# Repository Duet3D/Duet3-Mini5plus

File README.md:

# Duet3-Mini5+
The Duet 3 Mini 5+ balances value and performance, focused on small and medium size machines that do not need the high power output of the Duet 3 Mainboard 6HC. 

Product page is here: https://www.duet3d.com/Duet3Mini5plus

Documentation is here: https://docs.duet3d.com/Duet3D_hardware/Duet_3_family/Duet_3_Mini_5+_Hardware_Overview

This repository also contains information in the Mini 2+ : a two driver expansion board for the Duet 3 mini 5+

Product page is here: https://www.duet3d.com/Duet3ExpansionMini2plus

Documentation is here: https://docs.duet3d.com/Duet3D_hardware/Duet_3_family/Duet_3_Expansion_Mini_2+

As always please discuss this on the Duet3d forum: https://forum.duet3d.com/

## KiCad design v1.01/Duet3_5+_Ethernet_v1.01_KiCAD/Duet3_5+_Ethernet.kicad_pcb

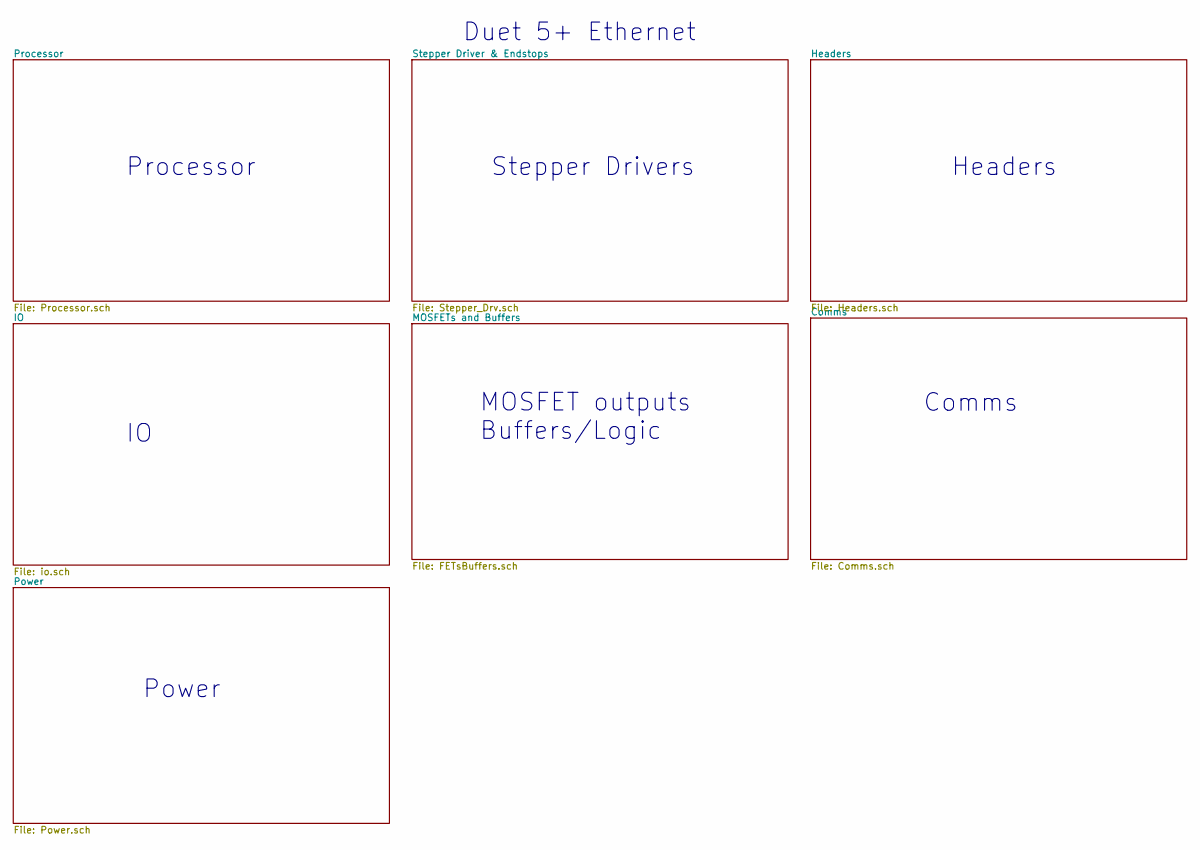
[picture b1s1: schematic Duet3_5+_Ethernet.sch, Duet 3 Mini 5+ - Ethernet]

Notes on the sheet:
Processor
Stepper Drivers
Headers
MOSFET outputs Buffers/Logic
Power
Duet 5+ Ethernet
Comms

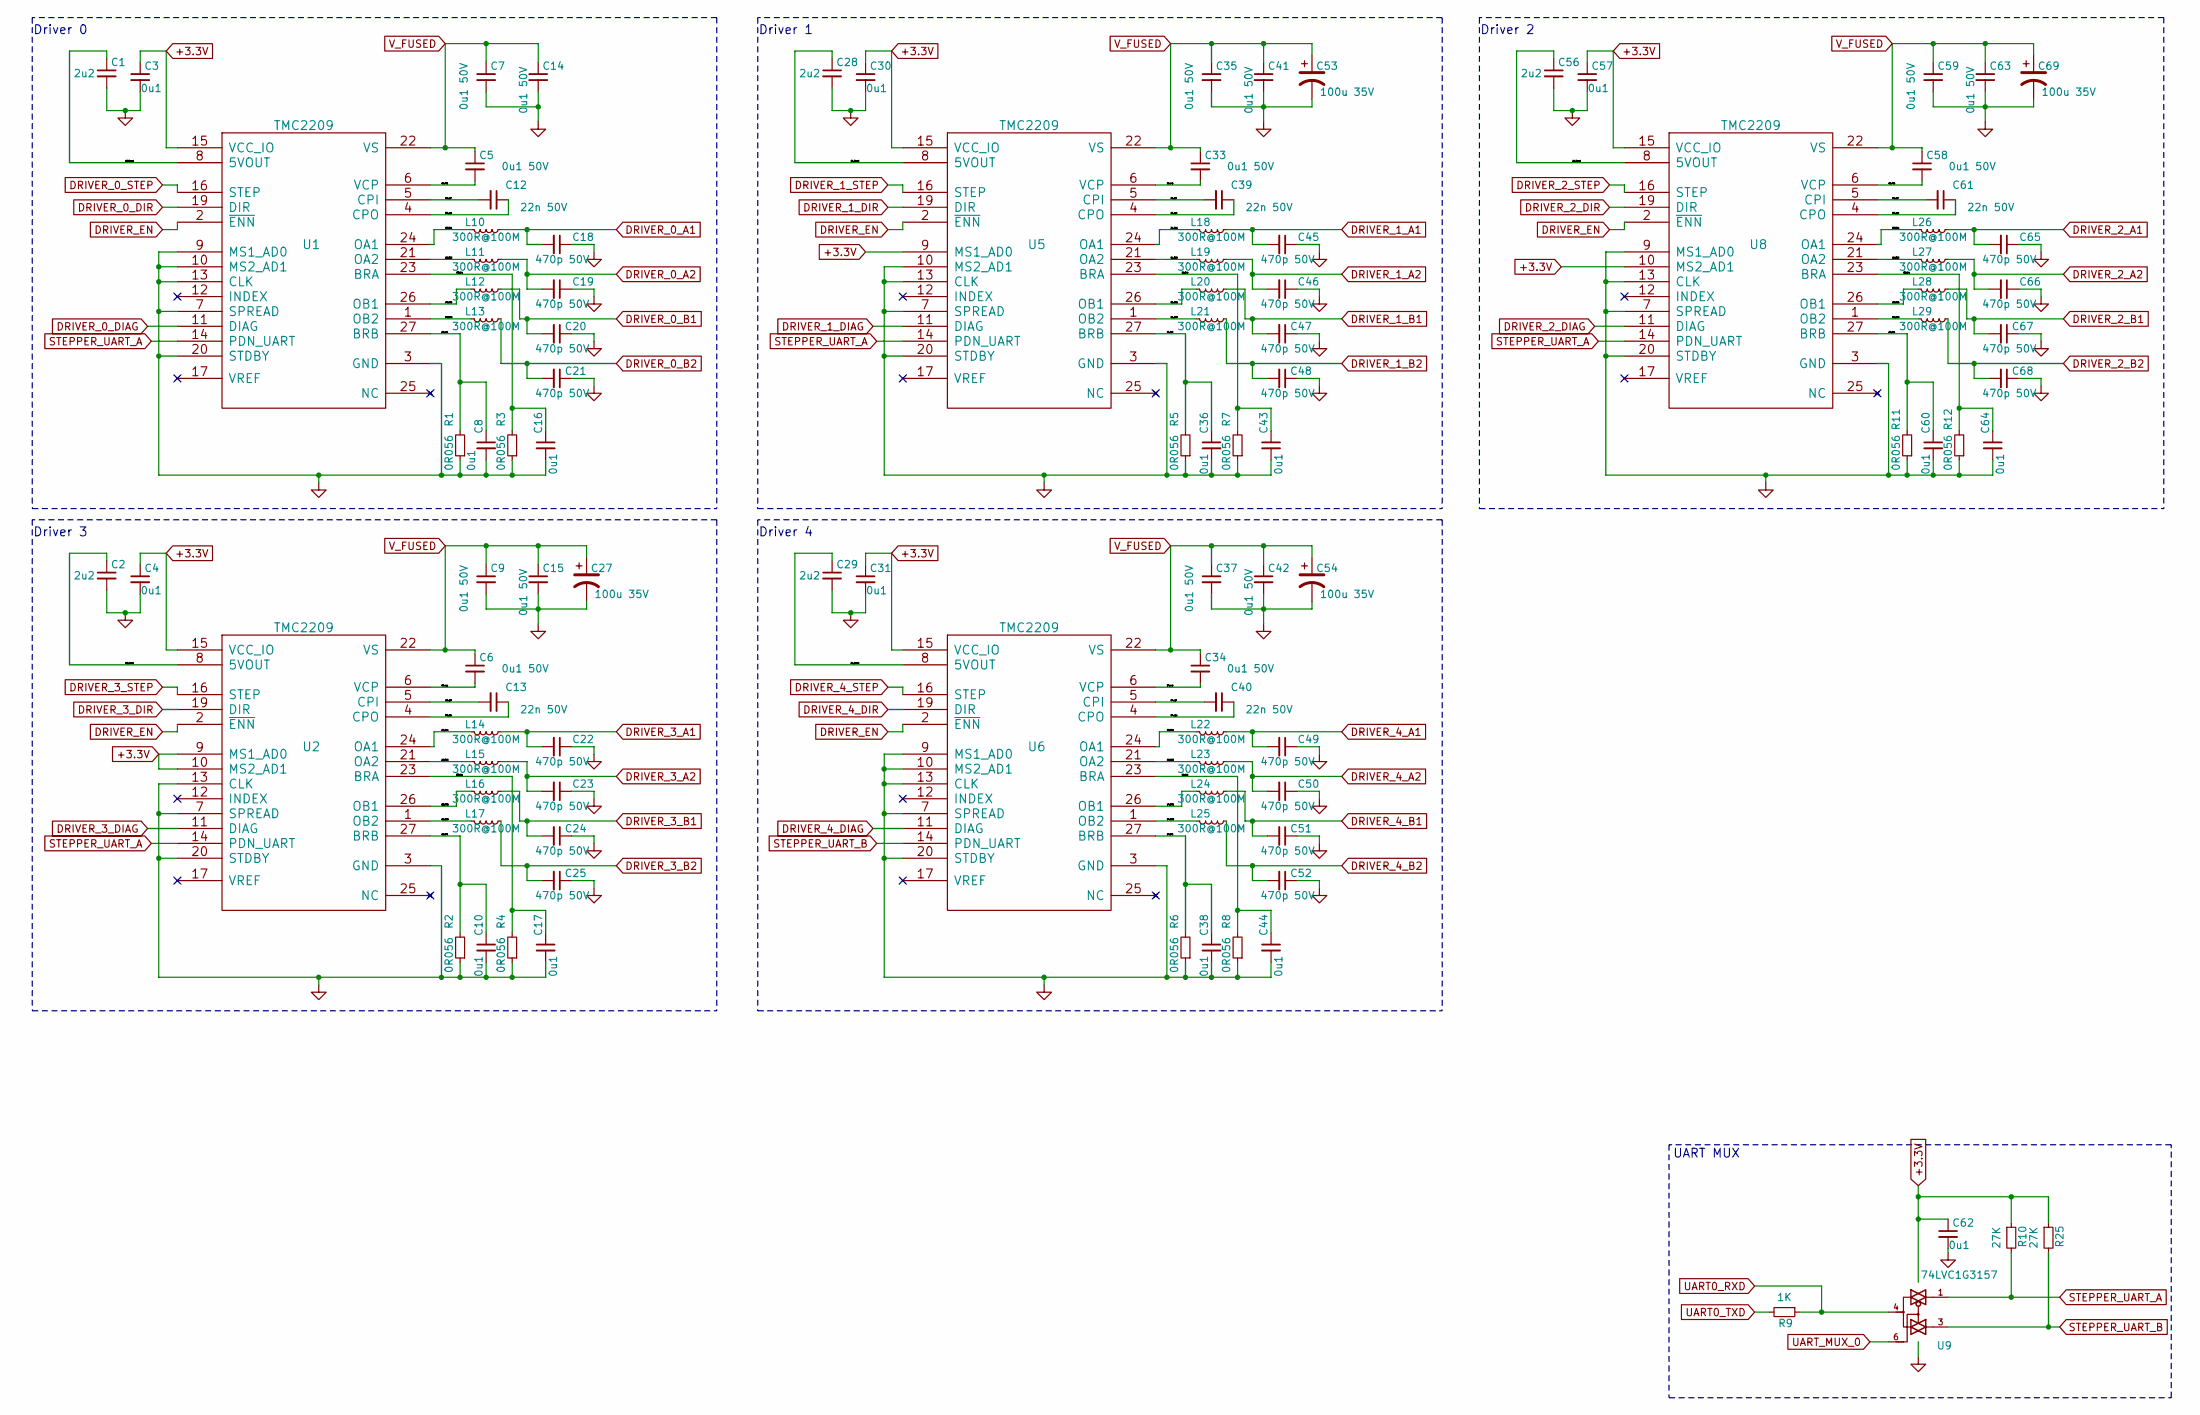
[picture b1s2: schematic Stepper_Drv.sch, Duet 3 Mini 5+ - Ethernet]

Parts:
C1, C2, C28, C29, C56: 2u2; C_0402_1005Metric_Wbry; Part Number LMK105BJ225KV-F or similar 10v+
C3, C4, C8, C10, C16, C17, C30, C31, C36, C38, C43, C44, C57, C60, C62, C64: 0u1; C_0402_1005Metric_Wbry; Part Number CL05A104KA5NNNC or similar
C5, C6, C7, C9, C14, C15, C33, C34, C35, C37, C41, C42, C58, C59, C63: 0u1 50V; C_0603_1608Metric_Wbry; Part Number CL10B104KB8NNNC
C12, C13, C39, C40, C61: 22n 50V; C_0402_1005Metric_Wbry; Part Number CC0402KRX7R9BB223
C18, C19, C20, C21, C22, C23, C24, C25, C45, C46, C47, C48, C49, C50, C51, C52, C65, C66, C67, C68: 470p 50V; C_0402_1005Metric_Wbry; Part Number CC0402KRX7R9BB471
C27, C53, C54, C69: 100u 35V; CP_Elec_6.3x7.7; Part Number e.g EEEFT1V101AP or 865080545012
L10, L11, L12, L13, L14, L15, L16, L17, L18, L19, L20, L21, L22, L23, L24, L25, L26, L27, L28, L29: 300R@100M; L_0603_1608Metric; Part Number 742792641 or similar
R1, R2, R3, R4, R5, R6, R7, R8, R11, R12: 0R056; R_0603_1608Metric_Wbry; Part Number 0603 0.33W or 0.5W 0.056R resistor
R9: 1K; R_0402_1005Metric_Wbry; Part Number RK73H1ETTP1001F
R10, R25: 27K; R_0402_1005Metric_Wbry; Part Number RK73H1ETTP2702F
U1, U2, U5, U6, U8: TMC2209; QFN-28-1EP_5x5mm_Pitch0.5mm; Part Number TMC2209-LA
U9: 74LVC1G3157; SOT-363_SC-70-6; Part Number 74LVC1G3157DW-7 (multiple options for 6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

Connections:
+3.3V: C3.1, C4.1, C30.1, C31.1, C57.1, C62.1, R10.1, R25.1, U1.15 (VCC_IO), U2.9 (MS1_AD0), U2.10 (MS2_AD1), U2.15 (VCC_IO), U5.9 (MS1_AD0), U5.15 (VCC_IO), U6.15 (VCC_IO), U8.10 (MS2_AD1), U8.15 (VCC_IO), U9.5 (VCC); also elsewhere on the board
/Stepper Driver & Endstops/D0_5vout: C1.1, U1.8 (5VOUT)
/Stepper Driver & Endstops/D0_OA1: L10.2, U1.24 (OA1)
/Stepper Driver & Endstops/D0_OA2: L11.2, U1.21 (OA2)
/Stepper Driver & Endstops/D0_OB1: L12.2, U1.26 (OB1)
/Stepper Driver & Endstops/D0_OB2: L13.2, U1.1 (OB2)
/Stepper Driver & Endstops/D0_bra: C16.1, R3.2, U1.23 (BRA)
/Stepper Driver & Endstops/D0_brb: C8.1, R1.2, U1.27 (BRB)
/Stepper Driver & Endstops/D0_cpi: C12.2, U1.5 (CPI)
/Stepper Driver & Endstops/D0_cpo: C12.1, U1.4 (CPO)
/Stepper Driver & Endstops/D0_vcp: C5.2, U1.6 (VCP)
/Stepper Driver & Endstops/D1_5vout: C28.1, U5.8 (5VOUT)
/Stepper Driver & Endstops/D1_OA1: L18.2, U5.24 (OA1)
/Stepper Driver & Endstops/D1_OA2: L19.2, U5.21 (OA2)
/Stepper Driver & Endstops/D1_OB1: L20.2, U5.26 (OB1)
/Stepper Driver & Endstops/D1_OB2: L21.2, U5.1 (OB2)
/Stepper Driver & Endstops/D1_bra: C43.1, R7.2, U5.23 (BRA)
/Stepper Driver & Endstops/D1_brb: C36.1, R5.2, U5.27 (BRB)
/Stepper Driver & Endstops/D1_cpi: C39.2, U5.5 (CPI)
/Stepper Driver & Endstops/D1_cpo: C39.1, U5.4 (CPO)
/Stepper Driver & Endstops/D1_vcp: C33.2, U5.6 (VCP)
/Stepper Driver & Endstops/D2_5vout: C56.1, U8.8 (5VOUT)
/Stepper Driver & Endstops/D2_OA1: L26.2, U8.24 (OA1)
/Stepper Driver & Endstops/D2_OA2: L27.2, U8.21 (OA2)
/Stepper Driver & Endstops/D2_OB1: L28.2, U8.26 (OB1)
/Stepper Driver & Endstops/D2_OB2: L29.2, U8.1 (OB2)
/Stepper Driver & Endstops/D2_bra: C64.1, R12.2, U8.23 (BRA)
/Stepper Driver & Endstops/D2_brb: C60.1, R11.2, U8.27 (BRB)
/Stepper Driver & Endstops/D2_cpi: C61.2, U8.5 (CPI)
/Stepper Driver & Endstops/D2_cpo: C61.1, U8.4 (CPO)
/Stepper Driver & Endstops/D2_vcp: C58.2, U8.6 (VCP)
/Stepper Driver & Endstops/D3_5vout: C2.1, U2.8 (5VOUT)
/Stepper Driver & Endstops/D3_OA1: L14.2, U2.24 (OA1)
/Stepper Driver & Endstops/D3_OA2: L15.2, U2.21 (OA2)
/Stepper Driver & Endstops/D3_OB1: L16.2, U2.26 (OB1)
/Stepper Driver & Endstops/D3_OB2: L17.2, U2.1 (OB2)
/Stepper Driver & Endstops/D3_bra: C17.1, R4.2, U2.23 (BRA)
/Stepper Driver & Endstops/D3_brb: C10.1, R2.2, U2.27 (BRB)
/Stepper Driver & Endstops/D3_cpi: C13.2, U2.5 (CPI)
/Stepper Driver & Endstops/D3_cpo: C13.1, U2.4 (CPO)
/Stepper Driver & Endstops/D3_vcp: C6.2, U2.6 (VCP)
/Stepper Driver & Endstops/D4_5vout: C29.1, U6.8 (5VOUT)
/Stepper Driver & Endstops/D4_OA1: L22.2, U6.24 (OA1)
/Stepper Driver & Endstops/D4_OA2: L23.2, U6.21 (OA2)
/Stepper Driver & Endstops/D4_OB1: L24.2, U6.26 (OB1)
/Stepper Driver & Endstops/D4_OB2: L25.2, U6.1 (OB2)
/Stepper Driver & Endstops/D4_bra: C44.1, R8.2, U6.23 (BRA)
/Stepper Driver & Endstops/D4_brb: C38.1, R6.2, U6.27 (BRB)
/Stepper Driver & Endstops/D4_cpi: C40.2, U6.5 (CPI)
/Stepper Driver & Endstops/D4_cpo: C40.1, U6.4 (CPO)
/Stepper Driver & Endstops/D4_vcp: C34.2, U6.6 (VCP)
DRIVER_0_A1: C18.2, L10.1; also elsewhere on the board
DRIVER_0_A2: C19.2, L11.1; also elsewhere on the board
DRIVER_0_B1: C20.2, L12.1; also elsewhere on the board
DRIVER_0_B2: C21.2, L13.1; also elsewhere on the board
DRIVER_0_DIAG: U1.11 (DIAG); also elsewhere on the board
DRIVER_0_DIR: U1.19 (DIR); also elsewhere on the board
DRIVER_0_STEP: U1.16 (STEP); also elsewhere on the board
DRIVER_1_A1: C45.2, L18.1; also elsewhere on the board
DRIVER_1_A2: C46.2, L19.1; also elsewhere on the board
DRIVER_1_B1: C47.2, L20.1; also elsewhere on the board
DRIVER_1_B2: C48.2, L21.1; also elsewhere on the board
DRIVER_1_DIAG: U5.11 (DIAG); also elsewhere on the board
DRIVER_1_DIR: U5.19 (DIR); also elsewhere on the board
DRIVER_1_STEP: U5.16 (STEP); also elsewhere on the board
DRIVER_2_A1: C65.2, L26.1; also elsewhere on the board
DRIVER_2_A2: C66.2, L27.1; also elsewhere on the board
DRIVER_2_B1: C67.2, L28.1; also elsewhere on the board
DRIVER_2_B2: C68.2, L29.1; also elsewhere on the board
DRIVER_2_DIAG: U8.11 (DIAG); also elsewhere on the board
DRIVER_2_DIR: U8.19 (DIR); also elsewhere on the board
DRIVER_2_STEP: U8.16 (STEP); also elsewhere on the board
DRIVER_3_A1: C22.2, L14.1; also elsewhere on the board
DRIVER_3_A2: C23.2, L15.1; also elsewhere on the board
DRIVER_3_B1: C24.2, L16.1; also elsewhere on the board
DRIVER_3_B2: C25.2, L17.1; also elsewhere on the board
DRIVER_3_DIAG: U2.11 (DIAG); also elsewhere on the board
DRIVER_3_DIR: U2.19 (DIR); also elsewhere on the board
DRIVER_3_STEP: U2.16 (STEP); also elsewhere on the board
DRIVER_4_A1: C49.2, L22.1; also elsewhere on the board
DRIVER_4_A2: C50.2, L23.1; also elsewhere on the board
DRIVER_4_B1: C51.2, L24.1; also elsewhere on the board
DRIVER_4_B2: C52.2, L25.1; also elsewhere on the board
DRIVER_4_DIAG: U6.11 (DIAG); also elsewhere on the board
DRIVER_4_DIR: U6.19 (DIR); also elsewhere on the board
DRIVER_4_STEP: U6.16 (STEP); also elsewhere on the board
DRIVER_EN: U1.2 (~ENN), U2.2 (~ENN), U5.2 (~ENN), U6.2 (~ENN), U8.2 (~ENN); also elsewhere on the board
GND: C1.2, C2.2, C3.2, C4.2, C7.2, C8.2, C9.2, C10.2, C14.2, C15.2, C16.2, C17.2, C18.1, C19.1, C20.1, C21.1, C22.1, C23.1, C24.1, C25.1, C27.2, C28.2, C29.2, C30.2, C31.2, C35.2, C36.2, C37.2, C38.2, C41.2, C42.2, C43.2, C44.2, C45.1, C46.1, C47.1, C48.1, C49.1, C50.1, C51.1, C52.1, C53.2, C54.2, C56.2, C57.2, C59.2, C60.2, C62.2, C63.2, C64.2, C65.1, C66.1, C67.1, C68.1, C69.2, R1.1, R2.1, R3.1, R4.1, R5.1, R6.1, R7.1, R8.1, R11.1, R12.1, U1.3 (GND), U1.7 (SPREAD), U1.9 (MS1_AD0), U1.10 (MS2_AD1), U1.13 (CLK), U1.18 (GND), U1.20 (STDBY), U1.29 (GND), U2.3 (GND), U2.7 (SPREAD), U2.13 (CLK), U2.18 (GND), U2.20 (STDBY), U2.29 (GND), U5.3 (GND), U5.7 (SPREAD), U5.10 (MS2_AD1), U5.13 (CLK), U5.18 (GND), U5.20 (STDBY), U5.29 (GND), U6.3 (GND), U6.7 (SPREAD), U6.9 (MS1_AD0), U6.10 (MS2_AD1), U6.13 (CLK), U6.18 (GND), U6.20 (STDBY), U6.29 (GND), U8.3 (GND), U8.7 (SPREAD), U8.9 (MS1_AD0), U8.13 (CLK), U8.18 (GND), U8.20 (STDBY), U8.29 (GND), U9.2 (GND); also elsewhere on the board
STEPPER_UART_A: R10.2, U1.14 (PDN_UART), U2.14 (PDN_UART), U5.14 (PDN_UART), U8.14 (PDN_UART), U9.1
STEPPER_UART_B: R25.2, U6.14 (PDN_UART), U9.3; also elsewhere on the board
UART0_RXD: R9.1, U9.4; also elsewhere on the board
UART0_TXD: R9.2; also elsewhere on the board
UART_MUX_0: U9.6; also elsewhere on the board
V_FUSED: C5.1, C6.1, C7.1, C9.1, C14.1, C15.1, C27.1, C33.1, C34.1, C35.1, C37.1, C41.1, C42.1, C53.1, C54.1, C58.1, C59.1, C63.1, C69.1, U1.22 (VS), U1.28 (VS), U2.22 (VS), U2.28 (VS), U5.22 (VS), U5.28 (VS), U6.22 (VS), U6.28 (VS), U8.22 (VS), U8.28 (VS); also elsewhere on the board

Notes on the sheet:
Driver 0
UART MUX
Driver 1
Driver 2
Driver 3
Driver 4

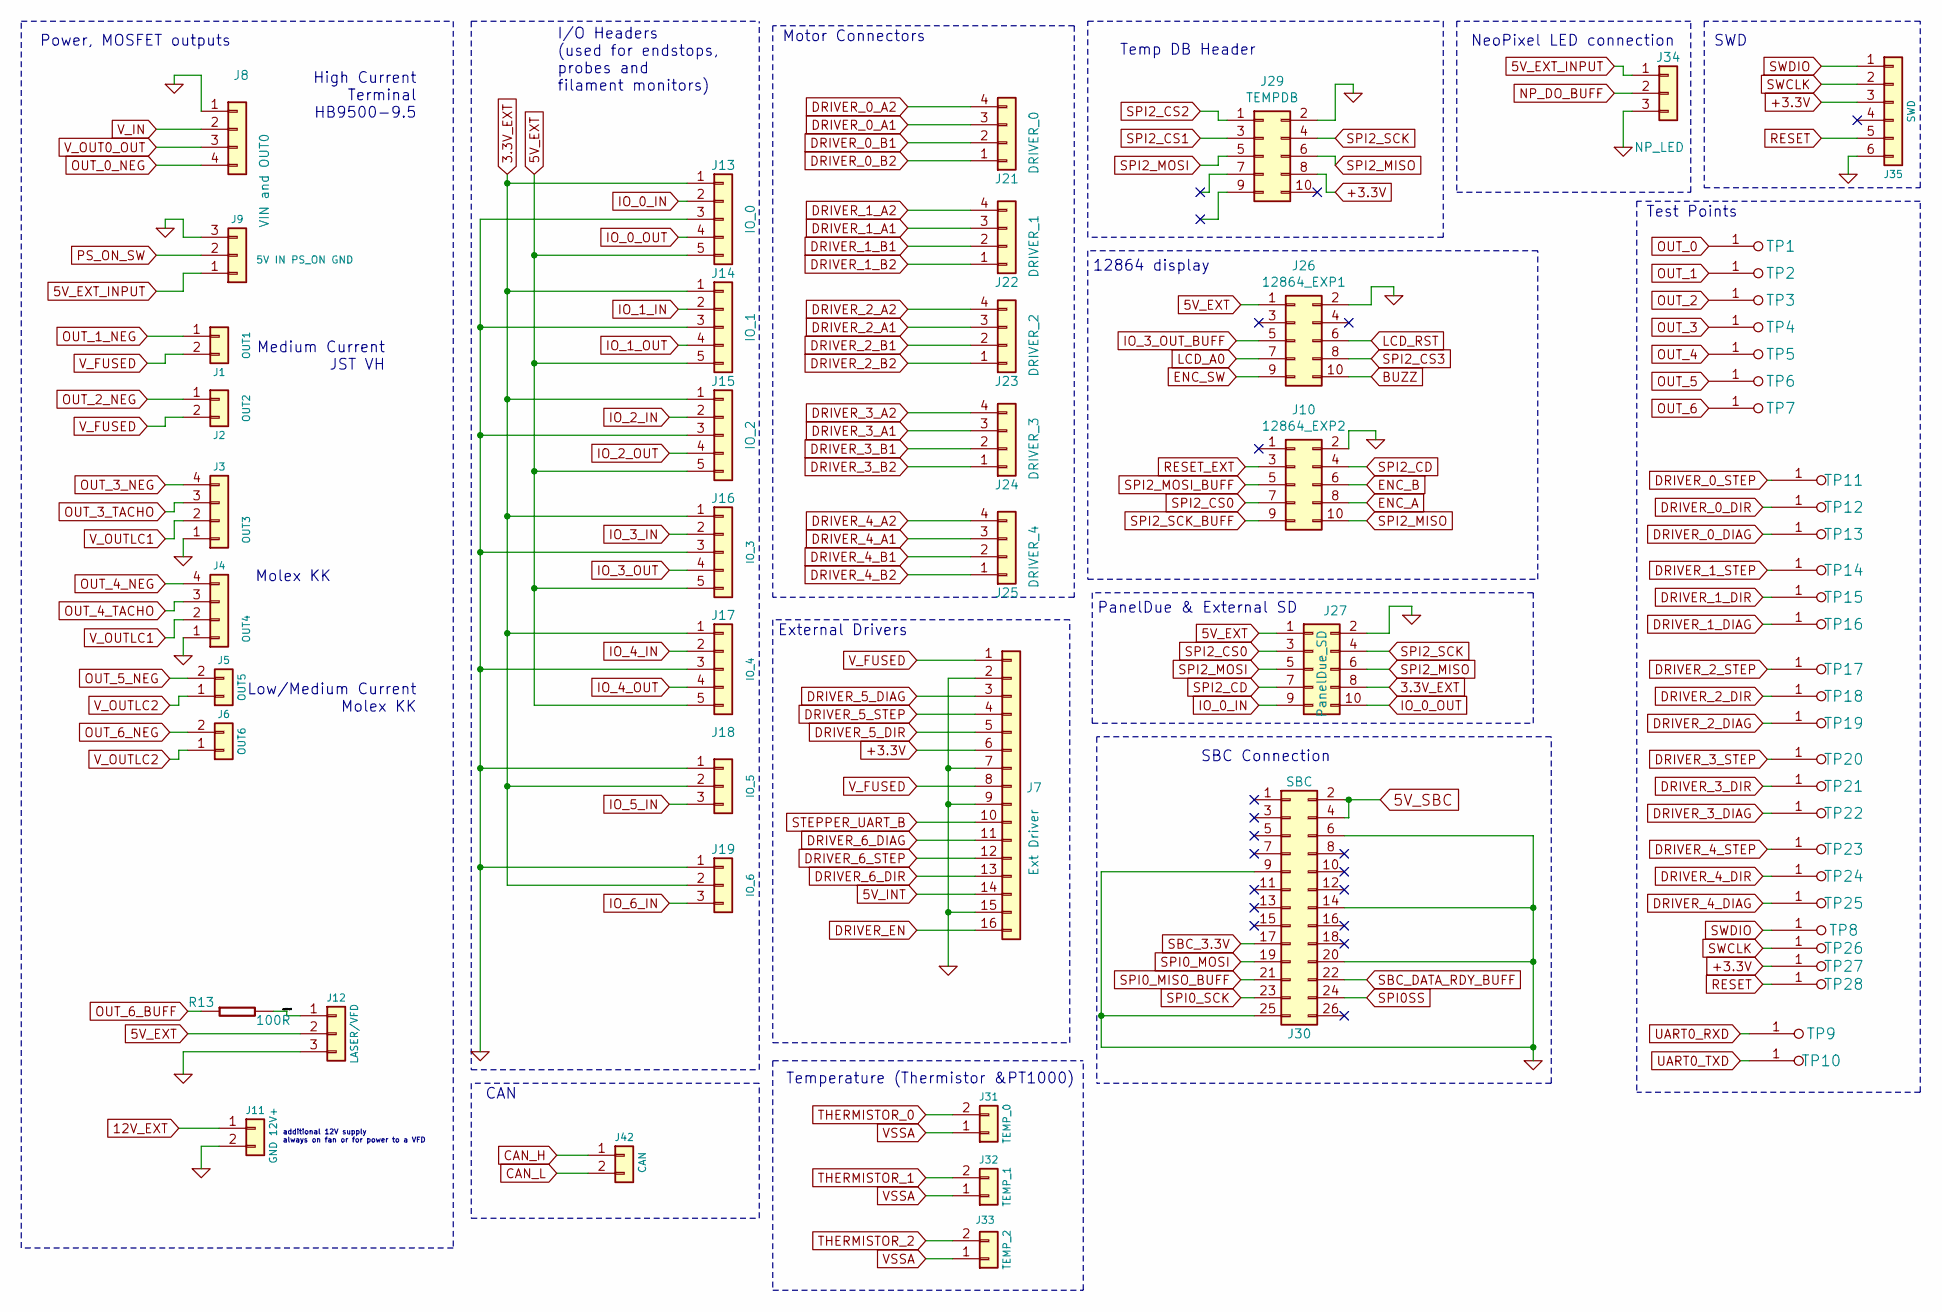
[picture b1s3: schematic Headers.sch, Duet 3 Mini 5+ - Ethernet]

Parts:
J1: OUT1; JST_VH_B2P-VH-B_1x02_P3.96mm_Vertical; Part Number B2P-VH(LF)(SN)
J2: OUT2; JST_VH_B2P-VH-B_1x02_P3.96mm_Vertical; Part Number B2P-VH(LF)(SN)
J3: OUT3; Wurth_61900411121-1x04_P2.54mm_Vertical(Molex_KK-254_AE-641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; Part Number 61900411121
J4: OUT4; Wurth_61900411121-1x04_P2.54mm_Vertical(Molex_KK-254_AE-641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; Part Number 61900411121
J5: OUT5; Wurth_61900211121-1x02_P2.54mm_Vertical-(Molex_KK-254_AE-64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; Part Number 61900211121
J6: OUT6; Wurth_61900211121-1x02_P2.54mm_Vertical-(Molex_KK-254_AE-64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; Part Number 61900211121
J7: Ext Driver; D3_mini2Plus_expansion_1x16; Part Number THS-20-R
J8: VIN and OUT0; screwt-barrier-9.5mm-1x4; Part Number HB950-9.50-4P
J9: 5V IN PS_ON GND; Wurth_61900311121-1x03_P2.54mm_Vertical(Molex_KK-254_AE-641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; Part Number 61900311121
J10: 12864_EXP2; IDC-Header_2x05_P2.54mm_Vertical; Part Number 302-S-10-D1R1
J11: GND 12V+; Wurth_61900211121-1x02_P2.54mm_Vertical-(Molex_KK-254_AE-64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; Part Number 61900211121
J12: LASER/VFD; Wurth_61900311121-1x03_P2.54mm_Vertical(Molex_KK-254_AE-641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; Part Number 61900311121
J13: IO_0; Wurth_61900511121-1x05_P2.54mm_Vertical(Molex_KK-254_AE-641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; Part Number 61900511121
J14: IO_1; Wurth_61900511121-1x05_P2.54mm_Vertical(Molex_KK-254_AE-641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; Part Number 61900511121
J15: IO_2; Wurth_61900511121-1x05_P2.54mm_Vertical(Molex_KK-254_AE-641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; Part Number 61900511121
J16: IO_3; Wurth_61900511121-1x05_P2.54mm_Vertical(Molex_KK-254_AE-641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; Part Number 61900511121
J17: IO_4; Wurth_61900511121-1x05_P2.54mm_Vertical(Molex_KK-254_AE-641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; Part Number 61900511121
J18: IO_5; Wurth_61900311121-1x03_P2.54mm_Vertical(Molex_KK-254_AE-641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; Part Number 61900311121
J19: IO_6; Wurth_61900311121-1x03_P2.54mm_Vertical(Molex_KK-254_AE-641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; Part Number 61900311121
J21: DRIVER_0; Wurth_61900411121-1x04_P2.54mm_Vertical(Molex_KK-254_AE-641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; Part Number 61900411121
J22: DRIVER_1; Wurth_61900411121-1x04_P2.54mm_Vertical(Molex_KK-254_AE-641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; Part Number 61900411121
J23: DRIVER_2; Wurth_61900411121-1x04_P2.54mm_Vertical(Molex_KK-254_AE-641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; Part Number 61900411121
J24: DRIVER_3; Wurth_61900411121-1x04_P2.54mm_Vertical(Molex_KK-254_AE-641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; Part Number 61900411121
J25: DRIVER_4; Wurth_61900411121-1x04_P2.54mm_Vertical(Molex_KK-254_AE-641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; Part Number 61900411121
J26: 12864_EXP1; IDC-Header_2x05_P2.54mm_Vertical; Part Number 302-S-10-D1R1
J27: PanelDue_SD; IDC-Header_2x05_P2.54mm_Vertical; Part Number 302-S-10-D1R1
J29: TEMPDB; MAX_TEMP_DB; Part Number THD-05-R
J30: SBC; IDC-Header_2x13_P2.54mm_Vertical; Part Number 61202621621
J31: TEMP_0; Wurth_61900211121-1x02_P2.54mm_Vertical-(Molex_KK-254_AE-64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; Part Number 61900211121
J32: TEMP_1; Wurth_61900211121-1x02_P2.54mm_Vertical-(Molex_KK-254_AE-64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; Part Number 61900211121
J33: TEMP_2; Wurth_61900211121-1x02_P2.54mm_Vertical-(Molex_KK-254_AE-64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; Part Number 61900211121
J34: NP_LED; Wurth_61900311121-1x03_P2.54mm_Vertical(Molex_KK-254_AE-641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; Part Number 61900311121
J35: SWD; JST_ZH_1x06_P1.5_B6B-ZR-SM4-TF; Part Number DNP - B6B-ZR(LF)(SN)
J42: CAN; Wurth_61900211121-1x02_P2.54mm_Vertical-(Molex_KK-254_AE-64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; Part Number 61900211121
R13: 100R; R_0402_1005Metric_Wbry; Part Number RK73H1ETTP1000F
TP1: OUT_0; TestPoint_Pad_D1.0mm; Part Number DNP - Virtual component
TP2: OUT_1; TestPoint_Pad_D1.0mm; Part Number DNP - Virtual component
TP3: OUT_2; TestPoint_Pad_D1.0mm; Part Number DNP - Virtual component
TP4: OUT_3; TestPoint_Pad_D1.0mm; Part Number DNP - Virtual component
TP5: OUT_4; TestPoint_Pad_D1.0mm; Part Number DNP - Virtual component
TP6: OUT_5; TestPoint_Pad_D1.0mm; Part Number DNP - Virtual component
TP7: OUT_6; TestPoint_Pad_D1.0mm; Part Number DNP - Virtual component
TP8: SWDIO; TestPoint_Pad_D1.5mm; Part Number DNP - Virtual component
TP9: UART0_RXD; TestPoint_Pad_D1.0mm; Part Number DNP - Virtual component
TP10: UART0_TXD; TestPoint_Pad_D1.0mm; Part Number DNP - Virtual component
TP11: D0_STEP; TestPoint_Pad_D1.0mm; Part Number DNP - Virtual component
TP12: D0_DIR; TestPoint_Pad_D1.0mm; Part Number DNP - Virtual component
TP13: D0_DIAG0; TestPoint_Pad_D1.0mm; Part Number DNP - Virtual component
TP14: D1_STEP; TestPoint_Pad_D1.0mm; Part Number DNP - Virtual component
TP15: D1_DIR; TestPoint_Pad_D1.0mm; Part Number DNP - Virtual component
TP16: D1_DIAG0; TestPoint_Pad_D1.0mm; Part Number DNP - Virtual component
TP17: D2_STEP; TestPoint_Pad_D1.0mm; Part Number DNP - Virtual component
TP18: D2_DIR; TestPoint_Pad_D1.0mm; Part Number DNP - Virtual component
TP19: D2_DIAG0; TestPoint_Pad_D1.0mm; Part Number DNP - Virtual component
TP20: D3_STEP; TestPoint_Pad_D1.0mm; Part Number DNP - Virtual component
TP21: D3_DIR; TestPoint_Pad_D1.0mm; Part Number DNP - Virtual component
TP22: D3_DIAG0; TestPoint_Pad_D1.0mm; Part Number DNP - Virtual component
TP23: D4_STEP; TestPoint_Pad_D1.0mm; Part Number DNP - Virtual component
TP24: D4_DIR; TestPoint_Pad_D1.0mm; Part Number DNP - Virtual component
TP25: D4_DIAG0; TestPoint_Pad_D1.0mm; Part Number DNP - Virtual component
TP26: SWCLK; TestPoint_Pad_D1.5mm; Part Number DNP - Virtual component
TP27: +3.3V; TestPoint_Pad_D1.5mm; Part Number DNP - Virtual component
TP28: RESET; TestPoint_Pad_D1.5mm; Part Number DNP - Virtual component

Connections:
3.3V_EXT: J13.1, J14.1, J15.1, J16.1, J17.1, J18.2, J19.2, J27.8; also elsewhere on the board
5V_EXT: J12.2, J13.5, J14.5, J15.5, J16.5, J17.5, J26.1, J27.1; also elsewhere on the board
5V_EXT_INPUT: J9.1, J34.1; also elsewhere on the board
5V_INT: J7.14; also elsewhere on the board
5V_SBC: J30.2, J30.4; also elsewhere on the board
12V_EXT: J11.1; also elsewhere on the board
+3.3V: J7.6, J29.8, J35.3, TP27.1; also elsewhere on the board
/Headers/out6buff: J12.1, R13.2
BUZZ: J26.10; also elsewhere on the board
CAN_H: J42.1; also elsewhere on the board
CAN_L: J42.2; also elsewhere on the board
DRIVER_0_A1: J21.3; also elsewhere on the board
DRIVER_0_A2: J21.4; also elsewhere on the board
DRIVER_0_B1: J21.2; also elsewhere on the board
DRIVER_0_B2: J21.1; also elsewhere on the board
DRIVER_0_DIAG: TP13.1; also elsewhere on the board
DRIVER_0_DIR: TP12.1; also elsewhere on the board
DRIVER_0_STEP: TP11.1; also elsewhere on the board
DRIVER_1_A1: J22.3; also elsewhere on the board
DRIVER_1_A2: J22.4; also elsewhere on the board
DRIVER_1_B1: J22.2; also elsewhere on the board
DRIVER_1_B2: J22.1; also elsewhere on the board
DRIVER_1_DIAG: TP16.1; also elsewhere on the board
DRIVER_1_DIR: TP15.1; also elsewhere on the board
DRIVER_1_STEP: TP14.1; also elsewhere on the board
DRIVER_2_A1: J23.3; also elsewhere on the board
DRIVER_2_A2: J23.4; also elsewhere on the board
DRIVER_2_B1: J23.2; also elsewhere on the board
DRIVER_2_B2: J23.1; also elsewhere on the board
DRIVER_2_DIAG: TP19.1; also elsewhere on the board
DRIVER_2_DIR: TP18.1; also elsewhere on the board
DRIVER_2_STEP: TP17.1; also elsewhere on the board
DRIVER_3_A1: J24.3; also elsewhere on the board
DRIVER_3_A2: J24.4; also elsewhere on the board
DRIVER_3_B1: J24.2; also elsewhere on the board
DRIVER_3_B2: J24.1; also elsewhere on the board
DRIVER_3_DIAG: TP22.1; also elsewhere on the board
DRIVER_3_DIR: TP21.1; also elsewhere on the board
DRIVER_3_STEP: TP20.1; also elsewhere on the board
DRIVER_4_A1: J25.3; also elsewhere on the board
DRIVER_4_A2: J25.4; also elsewhere on the board
DRIVER_4_B1: J25.2; also elsewhere on the board
DRIVER_4_B2: J25.1; also elsewhere on the board
DRIVER_4_DIAG: TP25.1; also elsewhere on the board
DRIVER_4_DIR: TP24.1; also elsewhere on the board
DRIVER_4_STEP: TP23.1; also elsewhere on the board
DRIVER_5_DIAG: J7.3; also elsewhere on the board
DRIVER_5_DIR: J7.5; also elsewhere on the board
DRIVER_5_STEP: J7.4; also elsewhere on the board
DRIVER_6_DIAG: J7.11; also elsewhere on the board
DRIVER_6_DIR: J7.13; also elsewhere on the board
DRIVER_6_STEP: J7.12; also elsewhere on the board
DRIVER_EN: J7.16; also elsewhere on the board
ENC_A: J10.8; also elsewhere on the board
ENC_B: J10.6; also elsewhere on the board
ENC_SW: J26.9; also elsewhere on the board
GND: J3.1, J4.1, J7.2, J7.7, J7.9, J7.15, J8.1, J9.3, J10.2, J11.2, J12.3, J13.3, J14.3, J15.3, J16.3, J17.3, J18.1, J19.1, J26.2, J27.2, J29.2, J30.6, J30.9, J30.14, J30.20, J30.25, J34.3, J35.6; also elsewhere on the board
IO_0_IN: J13.2, J27.9; also elsewhere on the board
IO_0_OUT: J13.4, J27.10; also elsewhere on the board
IO_1_IN: J14.2; also elsewhere on the board
IO_1_OUT: J14.4; also elsewhere on the board
IO_2_IN: J15.2; also elsewhere on the board
IO_2_OUT: J15.4; also elsewhere on the board
IO_3_IN: J16.2; also elsewhere on the board
IO_3_OUT: J16.4; also elsewhere on the board
IO_3_OUT_BUFF: J26.5; also elsewhere on the board
IO_4_IN: J17.2; also elsewhere on the board
IO_4_OUT: J17.4; also elsewhere on the board
IO_5_IN: J18.3; also elsewhere on the board
IO_6_IN: J19.3; also elsewhere on the board
LCD_A0: J26.7; also elsewhere on the board
LCD_RST: J26.6; also elsewhere on the board
NP_DO_BUFF: J34.2; also elsewhere on the board
OUT_0: TP1.1; also elsewhere on the board
OUT_0_NEG: J8.4; also elsewhere on the board
OUT_1: TP2.1; also elsewhere on the board
OUT_1_NEG: J1.1; also elsewhere on the board
OUT_2: TP3.1; also elsewhere on the board
OUT_2_NEG: J2.1; also elsewhere on the board
OUT_3: TP4.1; also elsewhere on the board
OUT_3_NEG: J3.4; also elsewhere on the board
OUT_3_TACHO: J3.3; also elsewhere on the board
OUT_4: TP5.1; also elsewhere on the board
OUT_4_NEG: J4.4; also elsewhere on the board
OUT_4_TACHO: J4.3; also elsewhere on the board
OUT_5: TP6.1; also elsewhere on the board
OUT_5_NEG: J5.2; also elsewhere on the board
OUT_6: TP7.1; also elsewhere on the board
OUT_6_BUFF: R13.1; also elsewhere on the board
OUT_6_NEG: J6.2; also elsewhere on the board
PS_ON_SW: J9.2; also elsewhere on the board
RESET: J35.5, TP28.1; also elsewhere on the board
RESET_EXT: J10.3; also elsewhere on the board
SBC_3.3V: J30.17; also elsewhere on the board
SBC_DATA_RDY_BUFF: J30.22; also elsewhere on the board
SPI0SS: J30.24; also elsewhere on the board
SPI0_MISO_BUFF: J30.21; also elsewhere on the board
SPI0_MOSI: J30.19; also elsewhere on the board
SPI0_SCK: J30.23; also elsewhere on the board
SPI2_CD: J10.4, J27.7; also elsewhere on the board
SPI2_CS0: J10.7, J27.3; also elsewhere on the board
SPI2_CS1: J29.3; also elsewhere on the board
SPI2_CS2: J29.1; also elsewhere on the board
SPI2_CS3: J26.8; also elsewhere on the board
SPI2_MISO: J10.10, J27.6, J29.6; also elsewhere on the board
SPI2_MOSI: J27.5, J29.5; also elsewhere on the board
SPI2_MOSI_BUFF: J10.5; also elsewhere on the board
SPI2_SCK: J27.4, J29.4; also elsewhere on the board
SPI2_SCK_BUFF: J10.9; also elsewhere on the board
STEPPER_UART_B: J7.10; also elsewhere on the board
SWCLK: J35.2, TP26.1; also elsewhere on the board
SWDIO: J35.1, TP8.1; also elsewhere on the board
THERMISTOR_0: J31.2; also elsewhere on the board
THERMISTOR_1: J32.2; also elsewhere on the board
THERMISTOR_2: J33.2; also elsewhere on the board
UART0_RXD: TP9.1; also elsewhere on the board
UART0_TXD: TP10.1; also elsewhere on the board
VSSA: J31.1, J32.1, J33.1; also elsewhere on the board
V_FUSED: J1.2, J2.2, J7.1, J7.8; also elsewhere on the board
V_IN: J8.2; also elsewhere on the board
V_OUT0_OUT: J8.3; also elsewhere on the board
V_OUTLC1: J3.2, J4.2; also elsewhere on the board
V_OUTLC2: J5.1, J6.1; also elsewhere on the board

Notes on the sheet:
High Current Terminal HB9500-9.5
Power, MOSFET outputs
Temperature (Thermistor &PT1000)
Motor Connectors
Test Points
Medium Current JST VH
Temp DB Header
Low/Medium Current Molex KK
I/O Headers (used for endstops, probes and filament monitors)
Molex KK
NeoPixel LED connection
SWD
SBC Connection
additional 12V supply always on fan or for power to a VFD
External Drivers
PanelDue & External SD
12864 display
CAN
